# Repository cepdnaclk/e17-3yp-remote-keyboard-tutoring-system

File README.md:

# Remote Keyboard Tutoring System

## Table of Contents
  - [Remote Keyboard Tutoring System](#remote-keyboard-tutoring-system)
  - [Table of Contents](#table-of-contents)
  - [Problem Overview](#problem-overview)
  - [Already Existing Approaches](#already-existing-approaches)
  - [Our Solution](#our-solution)
  - [Solution Architecture](#solution-architecture)
  - [Backend](#backend)
  - [Hardware Functionalities](#hardware-functionalities)
  - [Planned Features](#planned-features)
  - [Security Aspects](#security-aspects)
  - [Proposed Timeline](#proposed-timeline)
  - [Estimated Budget](#estimated-budget)
  - [Feedback](#feedback)
  - [Related Links](#related-links)

## Problem Overview

Piano is the most admired musical instrument so far. Over 25% of the world population fancy playing it. Yet not everyone is fortunate to learn from the best. This has fabricated a vast difference in the skill level of people who are playing the piano. The reason would be that most of the experts in the field lives in either the western hemisphere or east Asia. Even local experts aren't scattered throughout the island. So most of them tend to make use of the online procedures to teach piano. The current online methods would be using a platform like zoom and an app that simulates what one plays from his instrument.  Or else the student self learns just using an online app or tutorials. This hasn't shown profound results since the teacher or the student has problems when showing what he's playing on the piano in real time. The accuracy of the app isn't acceptable and the relationship between the student and the teacher isn't sturdy like in a live class room. Following problems occur due to an absence of a well-established remote method to teach or lean piano.

* A piano player has to be subtle. Several skills like hand / eye coordination, finger patterns, timing should be handled precisely.

* If teacher uses the online video streaming method to show what he plays on his piano, he might have to use several accessories (Ex: One camera to show his hand coordination, one camera to show his postures, a quality mic).

* People with a great potential might give up due to current ineffective ways to learn piano / keyboard online or not having a professional piano player to learn from his current location of residence.

## Already Existing Approaches

When it comes to online piano tutoring apps there are many popular apps for self-learning. Some of the popular apps are:

* [Skoove](https://www.skoove.com/en)
* [Yousician](https://yousician.com/)
* [Simply piano](https://www.joytunes.com/simply-piano)
* [Online Pianist](https://www.onlinepianist.com/)

All of them uses simulated keyboards to show the notes that the leaner should play and most of them uses the phone mic to get inputs to the app and give feedback to the player. These aren’t very accurate at giving you feedback since they can’t accurately identify the notes just using the microphone. The above applications _do not focus on remote real-time teaching_.

However, there are systems called [Piano Player Systems](https://www.amromusic.com/player-piano-systems) (or self playing pianos) which sort of do implement the above mentioned functionality. One example would be the [PianoDisc Piano Player](https://pianodisc.com/). These systems are mainly based on Pianos and not Keyboard Synthesizers. Thus, not everyone is able to afford those. Even though these systems can be used for remote tutoring purpose, they are mainly designed for entertainment purpose.

## Our Solution

The solution we present is a web based system that can be attached to any keyboard synthesizer through a MIDI connector (Legacy or USB). Thus, the only requirement for the keyboard is MIDI support. Once our system is connected to the keyboard, the user can interactively learn, play or teach in combination with the web application that we provide. The user has to be logged in as either a typical user or an expert depending on the user's needs. Users can get connected to each other in the network and they can share their music with each other. Users can play shared music in their own keyboard and join to experts to learn remotely in real-time. The tutor can handle multiple students at a time. When the tutor plays on the keyboard, those notes will be displayed and played in the students keyboards simultaneously. Tutor can upload exercises and when a student plays incorrectly, the wrong key presses will be displayed to both the student and the tutor.

## Solution Architecture

Our system consists of two devices: the _Pocessing Unit_ and the _Visualizer Bar_ which is a composition of _Visualizer Blocks_.

Processing Unit             |  Visualizer Bar
:--------------------------:|:-------------------------:
|  

The **Processing Unit** handles all the data processing and remote communications. It has two MIDI interfaces (one for MIDI-in and the other for MIDI-out) as well as two USB-C ports. The other USB port is to connect the visualizer bar in.

The **Visualizer Bar** is where all the key press information will be displayed at. The bar has to be placed on the keyboard near the end where the key hinges are. We provide the visualizer bar as easy-to-connect blocks in order for our product to fit any kind of keyboard and to make our product portable. The three common keyboard sizes are 61-keys, 76-keys and 88-keys. Therefore, the blocks are such that it covers an octave. Since blocks might not cover the whole keyboard, we provide the visualizer bar as a whole for the most common keyboard sizes as well. The visualizer bar has a USB-C port at the right end to connect in to the processing unit. The visualizer blocks have magnetic ends to stay still when they're connected. Left end of a block has a female USB-C port and the right end has a male USB-C connection. The bar has RGB leds representing each key and they will lit according to the key presses.

The above diagram shows an abstract diagram of how our system works.
Our solution consists of two main components: The Pocessing Unit and the Visualizer Bar 
The processing unit is connected to the keyboard via the MIDI interface and the processing unit is connected to the visualizer bar via a USB-C interface. The processing unit has inbuilt WI-FI as well as Bluetooth so the processing unit can directly connected to our server via a home router and exchange MIDI data with the server and with a another processing unit if they are connected in a same session. In order to communicate with the server we are going to implement a mobile as well as a web interface.

## Frontend

For our frontend web platform would be implemented using React.js. React will assure a fast and easy development of the frontend since React provides lots of readymade components to use and React uses javascript it will be easier to coordinate with the backend as well. Other than that React apps can be made SEO friendly by making them server-side rendered rather than client-side rendered.
Our frontend mobile platform will be implemented using Flutter since it also provides a lot of components to use and Flutter performs well in a lot of mobile devices. Since Flutter uses Dart as the programming language we can use the same codebase for both ios and android applications.
[Click here](./web-app) to see what we have done up to now in the web frontend.
[Click here](./Mobile%20App/rkt_mobile) to see what we have done so far in the mobile frontend. 

## Backend

Our backend computing platform would be Node.js along with express as the framework. It'll assist us in hadling multiple online requests and the working environment will be more effective and better-coordinated since javascript laguage is used in both frontend and backend development. MongoDB will be used as our database system. As the number of users for our product increase, it is very much practical to use MongoDB since it is very easy to scale up or down. MongoDB works on all types of cloud platforms. Since we'll be using aws to host our services MongoDB will be a great choice. NGINX is used as a reverse proxy so we can get access through http, https and Let's Encrypt is used to get free SSL certificates. All our backend services will be hosted using AWS services. An AWS EC2 instance is used run all the processes and AWS backup will be used to automate and manage backups. 

[click here](./server/src) to see what we have done so far.

## Hardware Functionalities

When it comes to hardware used in our embedded system, the brain of our processing unit is the **ESP32 Development board**. There are several reasons why we chose this board over other alternatives: built-in Wifi connectivity with 150Mbps data rate, integrated Bluetooth low energy (BLE) connectivity very small and compact board and the power consumption is less. As shown in the above high-level diagram, we need to have a MIDI interface in between the visualizer bar and the keyboard synthesizer for communicating with **MIDI messages** ([What is MIDI?](https://github.com/cepdnaclk/e17-3yp-remote-keyboard-tutoring-system/tree/main/Research/MIDI%20Technology)). The processing unit will be connected to Wifi as well as to the mobile phone via bluetooth. We use this BT connection for the offline helper as well as to authenticate to a Wifi router.

When MIDI messages arrive at the processing unit either from the user's keyboard or from remotely through the server, the microcontroller will process them and send control signals to the visualizer bar appropriately. The  communication between the visualizer bar and the processing unit will happen via an USB interface through a wired connection. The visualizer bar will also need to send signals to the processing unit because in order to light up the correct key on the keyboard, the processing unit needs to know the positional information of the particular visualizer block. So, before the user starts using the system he needs to do a very simple calibration procedure: play both the first note and the last note one after the other that the visualizer bar covers when the app prompts and thereafter the processing unit will memorize which block is where. In order to achieve this, the visualizer bar will also require a microcontroller. We will be using an arduino pro micro for this purpose.

## Planned Features

* Low latency real-time key press indication.
* Easy to setup / connect.
* The visualizer bar will be non-disturbing to the user and it will also add some aesthetics to the keyboard.
* The system will support any kind of non-standard keyboard as long as the keyboard has MIDI support.
* Students can easily find teachers available near their area.
* Classes can be scheduled through the application.
The web application allows teachers to upload exercises which will be played on student’s keyboard as MIDI so that the students can go along with and practise.
* Students can record what they’re playing and submit to the teacher in order to evaluate their work.
* An offline helper which can give assistance with the exercises.
* Efficient real-time Video & Audio Streaming for classes.
* Posture tracking for improving student's posture while playing.
* Finger tracking to check if the students are following the correct hand posture.

Current progress on implemented features can be seen [here](https://github.com/cepdnaclk/e17-3yp-remote-keyboard-tutoring-system/tree/main/web-app)

## Security Aspects

Cybersecurity of connected embedded system devices has always been important. Since our system also involves sharing private information through the internet like passwords and online payments, we have taken extra care to ensure the security of the system. The following diagram shows how we have designed our system to ensure the CIA triad.

The following diagram shows our secure embedded system design process. The gray color path is the ideal embedded system design process that anyone would follow. In addition to that, we have added a security approach that'll happen in parallel with the embedded system design process. Starting from our concept of operations, we will do a threat analysis while collecting the functional requirements to analyze the potential attacks that the system may be subjected to when deployed. The next step is to specify how our demand measures the security requirements of the system. Once we have the security requirements, we will start developing the security approach after some rounds of evaluations.

## Proposed Timeline

## Estimated Budget

## Feedback

✨ If you have any questions or suggestions for improvement regarding our project, feel free to share them [here](https://padlet.com/sathiiii/RKT_Discussion).✨

## Related Links

[University of Peradeniya](https://www.pdn.ac.lk/academics/academics.php/)

[Faculty of Engineering](http://eng.pdn.ac.lk/)

[Department of Computer Engineering](http://www.ce.pdn.ac.lk/)

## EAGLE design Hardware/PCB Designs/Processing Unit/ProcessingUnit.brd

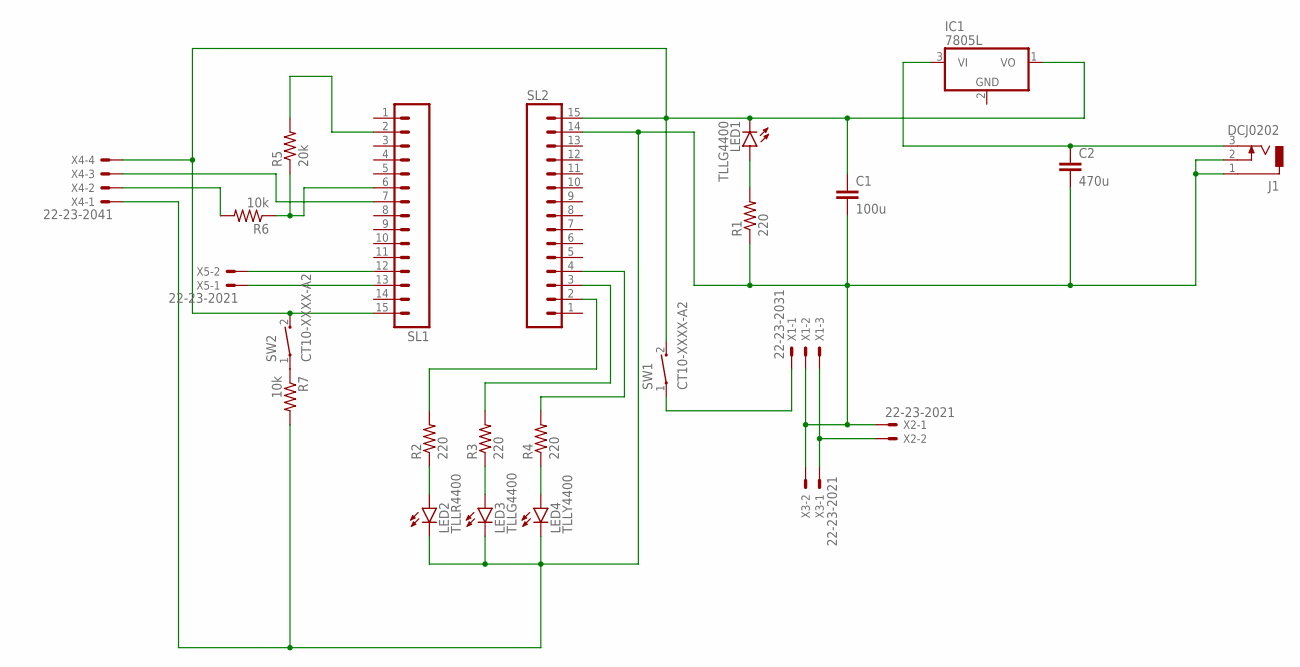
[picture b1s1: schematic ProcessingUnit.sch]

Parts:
C1: 100u; C025-025X050
C2: 470u; C025-025X050
IC1: 7805L; TO92
J1: DCJ0202
LED1, LED3: TLLG4400; LED3MM
LED2: TLLR4400; LED3MM
LED4: TLLY4400; LED3MM
R1, R2, R3, R4: 220; 0204/7
R5: 20k; 0204/7
R6, R7: 10k; 0204/7
SL1, SL2: M15; 15P
SW1, SW2: CT10-XXXX-A2
X1: 22-23-2031
X2, X3, X5: 22-23-2021
X4: 22-23-2041

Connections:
unnamed: SL1.13, X5.1
unnamed: R5.2, SL1.2
unnamed: LED1.A, R1.2
unnamed: C2.1, IC1.3 (VI), J1.3
unnamed: SW1.1, X1.1
unnamed: LED2.A, R2.1
unnamed: X1.3, X2.2, X3.1
unnamed: R2.2, SL2.2
unnamed: R3.2, SL2.3
unnamed: R4.2, SL2.4
unnamed: LED3.A, R3.1
unnamed: LED4.A, R4.1
unnamed: C1.2, C2.2, J1.1, J1.2, LED2.K (C), LED3.K (C), LED4.K (C), R1.1, R7.2, SL2.14, X1.2, X2.1, X3.2, X4.1
unnamed: R5.1, R6.1, SL1.6
unnamed: R7.1, SW2.1
unnamed: R6.2, X4.2
unnamed: SL1.7, X4.3
unnamed: C1.1, IC1.1 (VO), LED1.K (C), SL1.15, SL2.15, SW1.2, SW2.2, X4.4
unnamed: SL1.12, X5.2

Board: 2 copper layers, 24 parts (0 on the bottom side), 19 nets, no tracks yet.

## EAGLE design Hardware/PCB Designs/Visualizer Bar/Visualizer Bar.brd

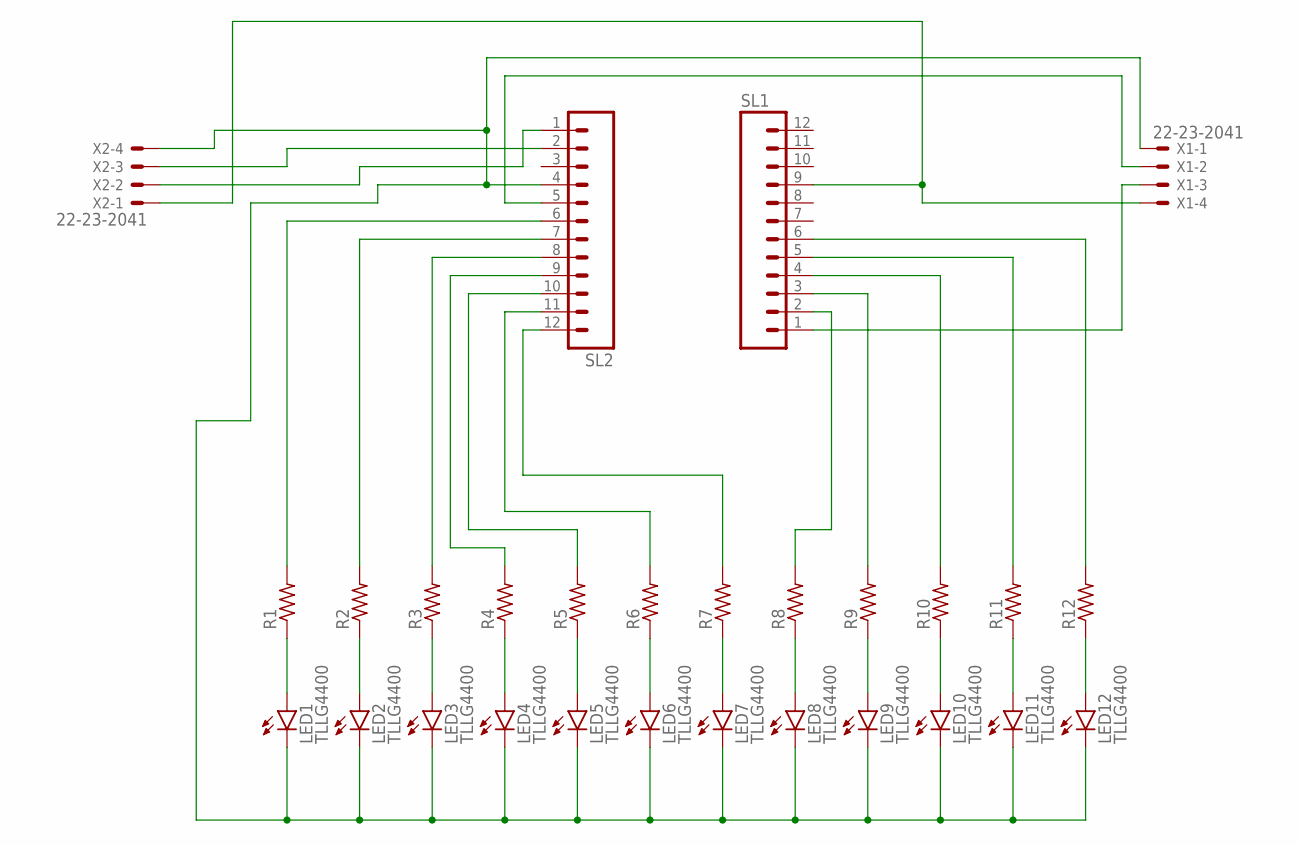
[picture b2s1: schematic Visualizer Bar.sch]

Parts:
LED1, LED2, LED3, LED4, LED5, LED6, LED7, LED8, LED9, LED10, LED11, LED12: TLLG4400; LED3MM
R1, R2, R3, R4, R5, R6, R7, R8, R9, R10, R11, R12: R-US_0204/5; 0204/5
SL1, SL2: M12; 12P
X1, X2: 22-23-2041

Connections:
unnamed: R6.2, SL2.11
unnamed: R4.2, SL2.9
unnamed: R3.2, SL2.8
unnamed: R5.2, SL2.10
unnamed: R2.2, SL2.7
unnamed: SL1.1, X1.3
unnamed: R12.2, SL1.6
unnamed: R11.2, SL1.5
unnamed: R10.2, SL1.4
unnamed: R9.2, SL1.3
unnamed: R8.2, SL1.2
unnamed: R7.2, SL2.12
unnamed: LED1.A, R1.1
unnamed: LED2.A, R2.1
unnamed: LED3.A, R3.1
unnamed: LED4.A, R4.1
unnamed: LED5.A, R5.1
unnamed: LED6.A, R6.1
unnamed: LED7.A, R7.1
unnamed: LED8.A, R8.1
unnamed: LED9.A, R9.1
unnamed: LED10.A, R10.1
unnamed: LED11.A, R11.1
unnamed: LED12.A, R12.1
unnamed: R1.2, SL2.6
unnamed: SL2.5, X1.2
unnamed: LED1.K (C), LED2.K (C), LED3.K (C), LED4.K (C), LED5.K (C), LED6.K (C), LED7.K (C), LED8.K (C), LED9.K (C), LED10.K (C), LED11.K (C), LED12.K (C), SL2.4, X1.1, X2.4
unnamed: SL1.9, X1.4, X2.1
unnamed: SL2.2, X2.3
unnamed: SL2.1, X2.2

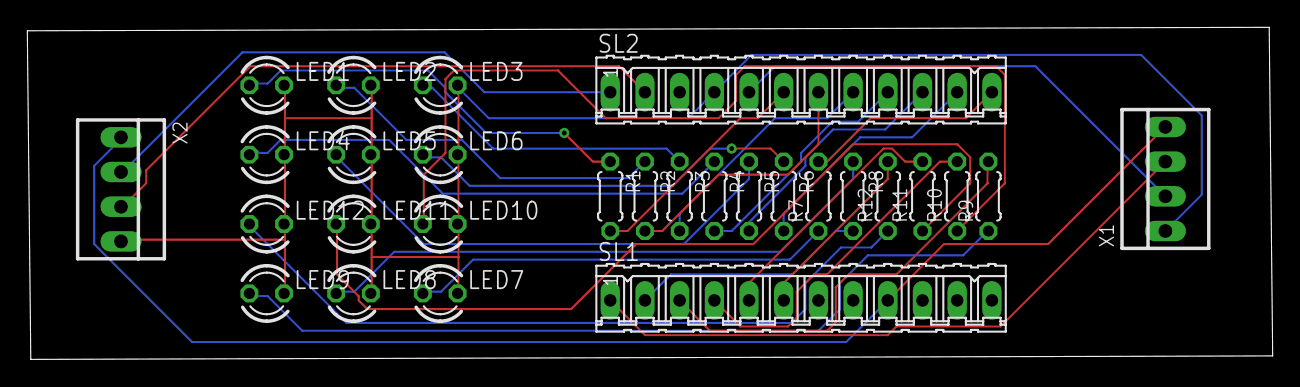
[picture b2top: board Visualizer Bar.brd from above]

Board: 2 copper layers, 91.2 x 24.3 mm, 28 parts (0 on the bottom side), 30 nets.

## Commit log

2022-10-06 Minor changes to the project web page
2022-11-11 Update schematics + firmware testing codes
2022-11-12 Added viaulizer Bar PCB eagle files
2022-11-13 File location changes
2022-11-13 Added the processing unit pcb designs
2022-11-15 Update master test firmware
2022-11-15 Update slave test firmware
2022-11-18 changes to the softwareserial master code
2022-11-21 Added firmware folder
2022-11-22 Firmware update
